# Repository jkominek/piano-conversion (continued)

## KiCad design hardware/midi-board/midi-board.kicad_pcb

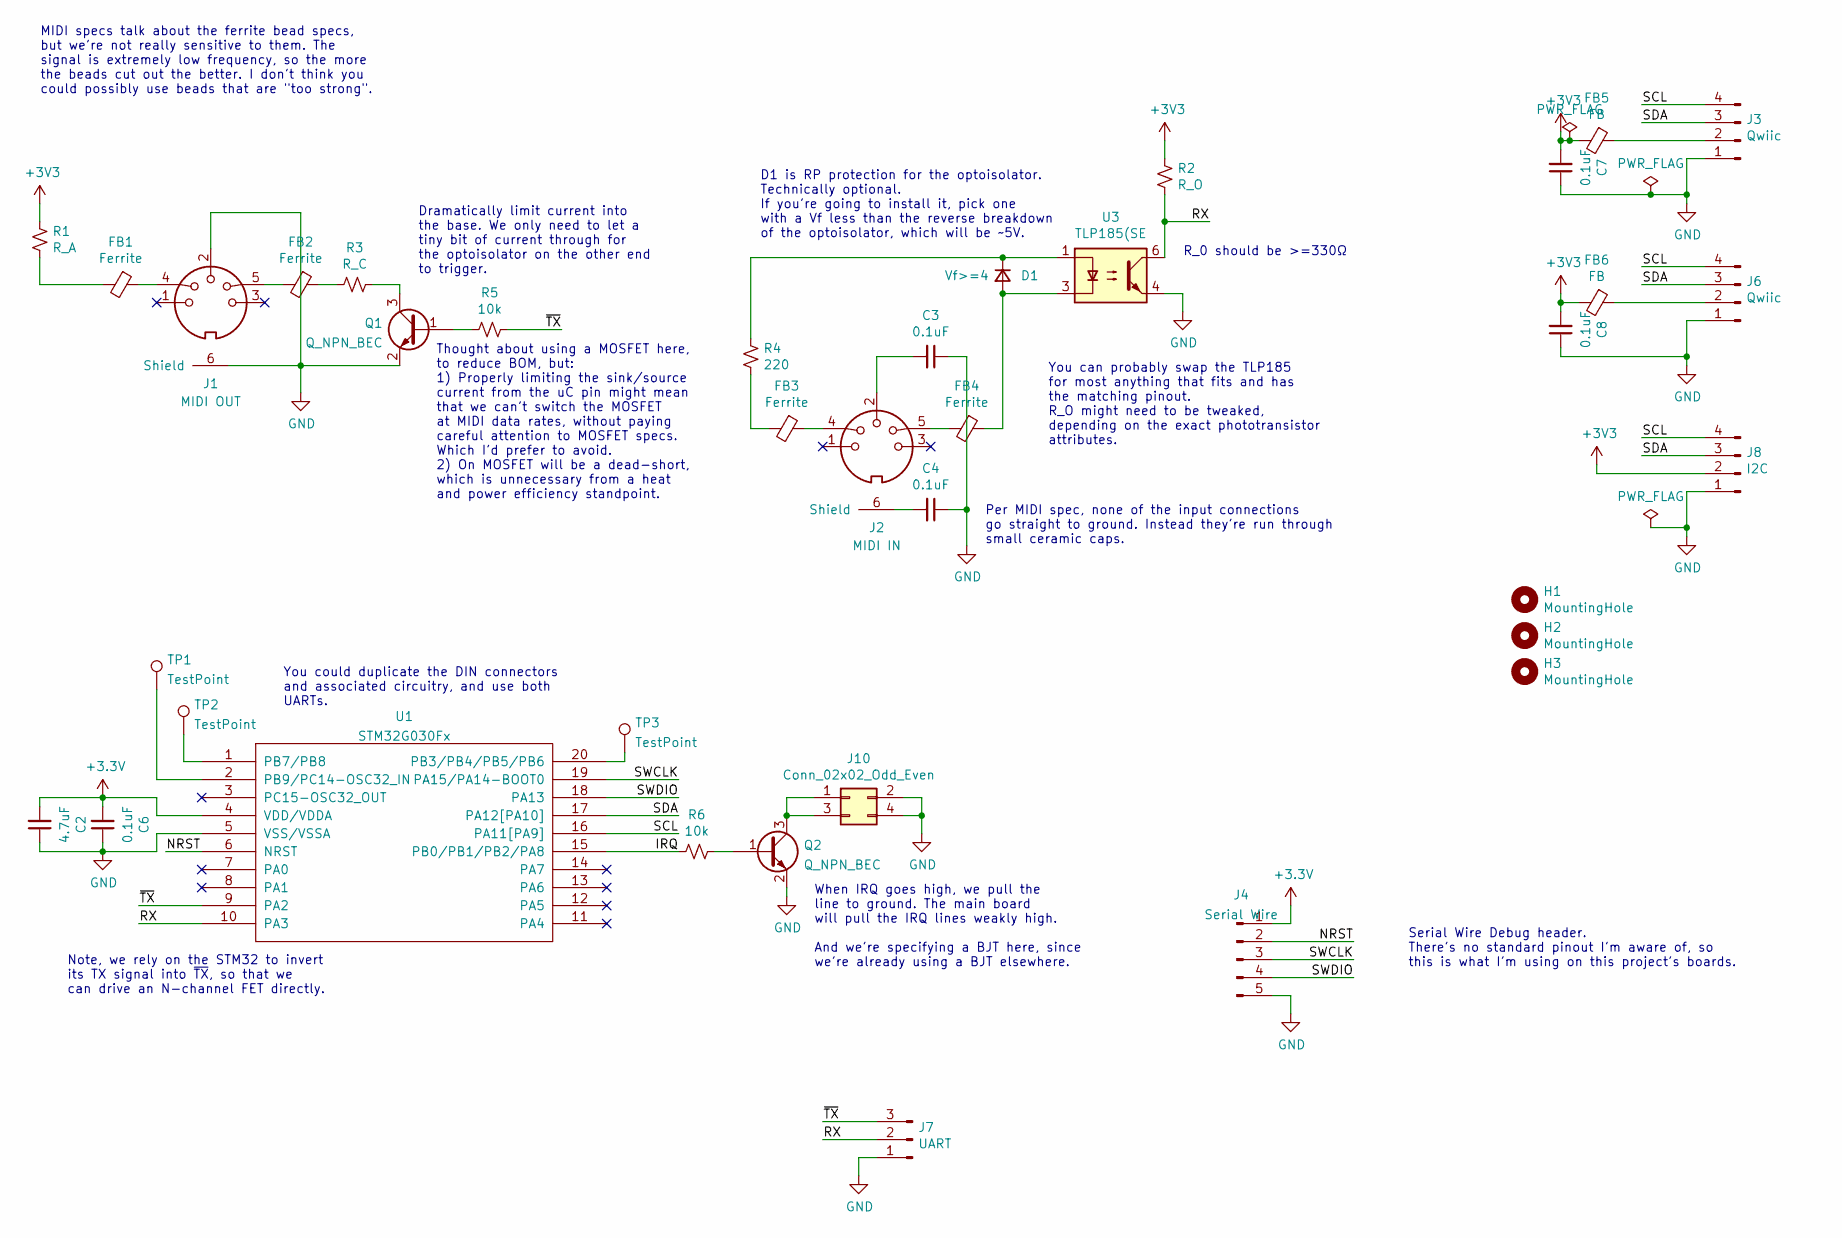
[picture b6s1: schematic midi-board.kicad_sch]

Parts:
C2: 4.7uF; C_0805_2012Metric_Pad1.18x1.45mm_HandSolder
C3, C4, C6, C7, C8: 0.1uF; C_0805_2012Metric_Pad1.18x1.45mm_HandSolder
D1: Vf>=4; D_SOD-123F
FB1, FB2, FB3, FB4: Ferrite; L_0805_2012Metric_Pad1.05x1.20mm_HandSolder
FB5, FB6: FB; L_0805_2012Metric_Pad1.05x1.20mm_HandSolder
H1, H2, H3: MountingHole; MountingHole_3.2mm_M3
J1: MIDI OUT; SDS-50J
J2: MIDI IN; SDS-50J
J3, J6: Qwiic; JST_SH_SM04B-SRSS-TB_04x1.00mm_Angled
J4: Serial Wire; PinHeader_1x05_P2.54mm_Vertical
J7: UART; Pin_Header_Straight_1x03_Pitch2.54mm
J8: I2C; Pin_Header_Straight_1x04_Pitch2.54mm
J10: Conn_02x02_Odd_Even; Pin_Header_Straight_2x02_Pitch2.54mm
Q1, Q2: Q_NPN_BEC; SOT-23
R1: R_A; R_0805_2012Metric_Pad1.20x1.40mm_HandSolder
R2: R_O; R_0805_2012Metric_Pad1.20x1.40mm_HandSolder
R3: R_C; R_0805_2012Metric_Pad1.20x1.40mm_HandSolder
R4: 220; R_0805_2012Metric_Pad1.20x1.40mm_HandSolder
R5, R6: 10k; R_0805_2012Metric_Pad1.20x1.40mm_HandSolder
TP1, TP2, TP3: TestPoint; TestPoint_Pad_D1.0mm
U1: STM32G030Fx; TSSOP-20_4.4x6.5mm_P0.65mm
U3: TLP185(SE; SO-6_4.4x3.6mm_Pitch1.27mm

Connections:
/IRQ: R6.2, U1.15 (PB0/PB1/PB2/PA8)
/NRST: J4.2, U1.6 (NRST)
/RX: J7.2, R2.2, U1.10 (PA3), U3.6
/SCL: J3.4, J6.4, J8.4, U1.16 (PA11[PA9])
/SDA: J3.3, J6.3, J8.3, U1.17 (PA12[PA10])
/SWCLK: J4.3, U1.19 (PA15/PA14-BOOT0)
/SWDIO: J4.4, U1.18 (PA13)
/~TX: J7.3, R5.1, U1.9 (PA2)
GND: C2.1, C3.1, C4.1, C6.1, C7.1, C8.1, J1.2, J1.6 (Shield), J3.1, J4.5, J6.1, J7.1, J8.1, J10.2, J10.4, Q1.2 (E), Q2.2 (E), U1.5 (VSS/VSSA), U3.4
unnamed: C3.2, J2.2
unnamed: C4.2, J2.6 (Shield)
unnamed: D1.1 (K), R4.1, U3.1
unnamed: D1.2 (A), FB4.1, U3.3
unnamed: FB1.1, J1.4
unnamed: FB1.2, R1.2
unnamed: FB2.1, R3.2
unnamed: FB2.2, J1.5
unnamed: FB3.1, J2.4
unnamed: FB3.2, R4.2
unnamed: FB4.2, J2.5
unnamed: FB5.1, J3.2
unnamed: FB6.1, J6.2
unnamed: J10.1, J10.3, Q2.3 (C)
unnamed: Q1.1 (B), R5.2
unnamed: Q1.3 (C), R3.1
unnamed: Q2.1 (B), R6.1
unnamed: TP1.1, U1.2 (PB9/PC14-OSC32_IN)
unnamed: TP2.1, U1.1 (PB7/PB8)
unnamed: TP3.1, U1.20 (PB3/PB4/PB5/PB6)

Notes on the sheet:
MIDI specs talk about the ferrite bead specs, but we're not really sensitive to them. The signal is extremely low frequency, so the more the beads cut out the better. I don't think you could possibly use beads that are "too strong".
When IRQ goes high, we pull the line to ground. The main board will pull the IRQ lines weakly high. And we're specifying a BJT here, since we're already using a BJT elsewhere.
R_0 should be >=330Ω
Per MIDI spec, none of the input connections go straight to ground. Instead they're run through small ceramic caps.
Note, we rely on the STM32 to invert its TX signal into ~{TX}, so that we can drive an N-channel FET directly.
You can probably swap the TLP185 for most anything that fits and has the matching pinout. R_O might need to be tweaked, depending on the exact phototransistor attributes.
Thought about using a MOSFET here, to reduce BOM, but: 1) Properly limiting the sink/source current from the uC pin might mean that we can't switch the MOSFET at MIDI data rates, without paying careful attention to MOSFET specs. Which I'd prefer to avoid. 2) On MOSFET will be a dead-short, which is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
Serial Wire Debug header. There's no standard pinout I'm aware of, so this is what I'm using on this project's boards.
D1 is RP protection for the optoisolator. Technically optional. If you're going to install it, pick one with a Vf less than the reverse breakdown of the optoisolator, which will be ~5V.
Dramatically limit current into the base. We only need to let a tiny bit of current through for the optoisolator on the other end to trigger.
You could duplicate the DIN connectors and associated circuitry, and use both UARTs.

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
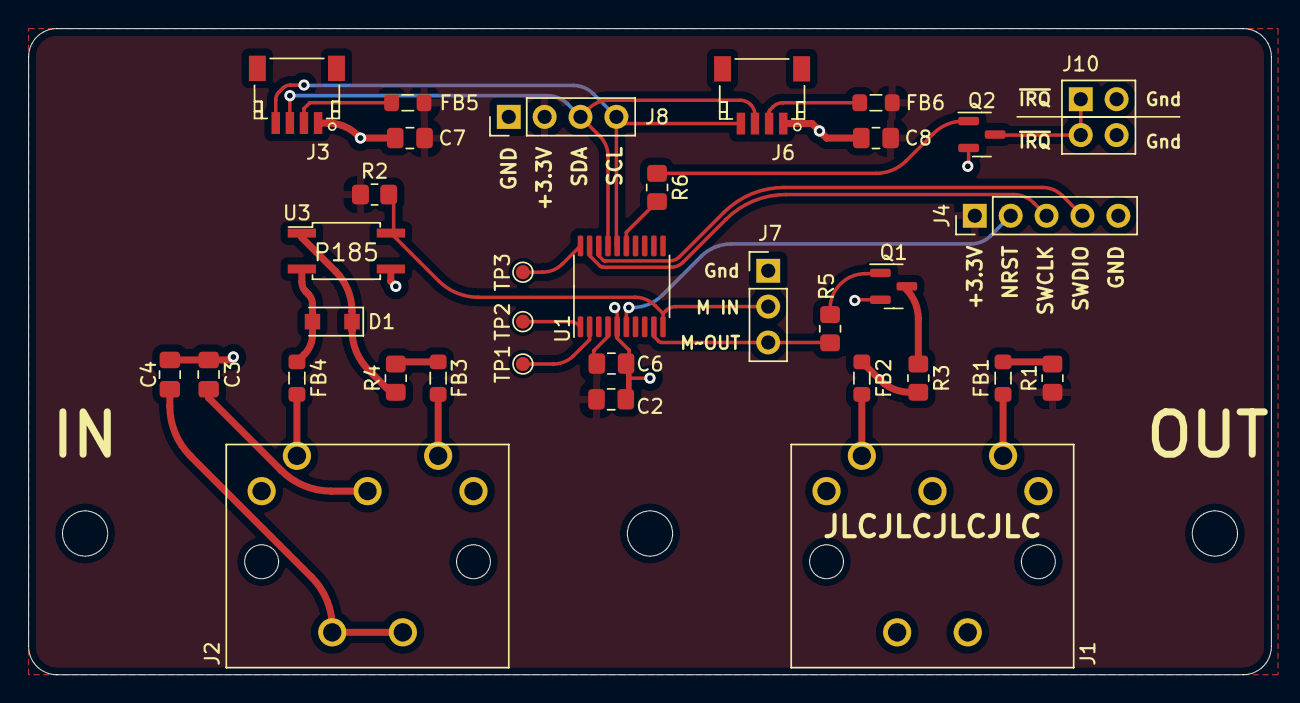
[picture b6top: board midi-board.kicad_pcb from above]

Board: 2 copper layers, 88.0 x 45.8 mm, 37 parts (0 on the bottom side), 30 nets.

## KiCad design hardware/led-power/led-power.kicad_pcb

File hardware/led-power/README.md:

# LED Power board

As covered in the main design doc, the board takes +48V, and uses them
to feed 8 strings of LEDs with a constant current of ~20mA.

# Design

See [the wiki page about the board](https://github.com/jkominek/piano-conversion/wiki/LED-Power-Board) for details on how it works.

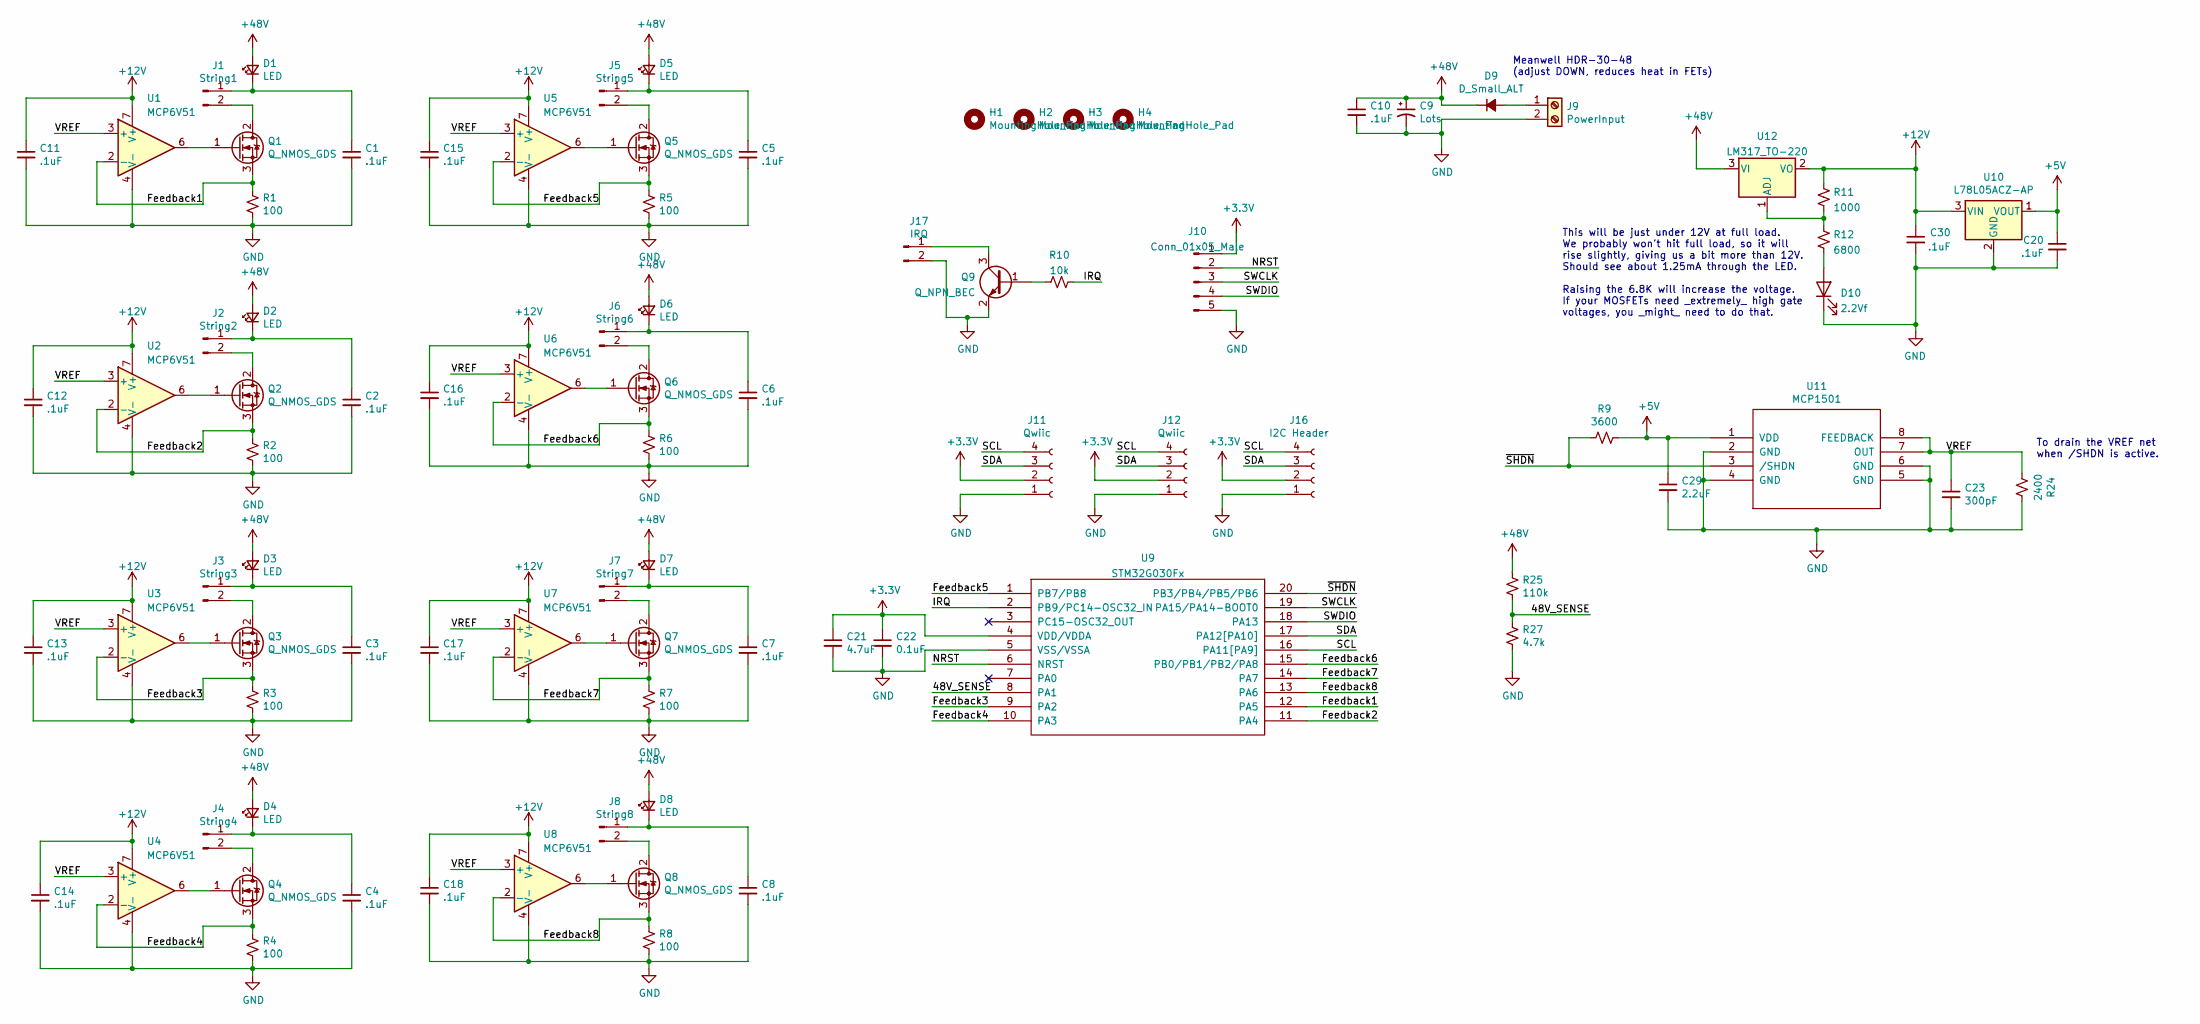
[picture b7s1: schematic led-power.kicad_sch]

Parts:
C1, C2, C3, C4, C5, C6, C7, C8, C10, C11, C12, C13, C14, C15, C16, C17, C18, C20, C30: .1uF; C_0805_2012Metric_Pad1.18x1.45mm_HandSolder
C9: Lots; CP_Radial_D16.0mm_P7.50mm
C21: 4.7uF; C_0805_2012Metric_Pad1.18x1.45mm_HandSolder
C22: 0.1uF; C_0805_2012Metric_Pad1.18x1.45mm_HandSolder
C23: 300pF; C_0805_2012Metric_Pad1.18x1.45mm_HandSolder
C29: 2.2uF; C_0805_2012Metric_Pad1.18x1.45mm_HandSolder
D1, D2, D3, D4, D5, D6, D7, D8: LED; LED_0805_2012Metric_Pad1.15x1.40mm_HandSolder
D9: D_Small_ALT; D_SOD-123F
D10: 2.2Vf; LED_0805_2012Metric_Pad1.15x1.40mm_HandSolder
H1, H2, H3, H4: MountingHole_Pad; MountingHole_3.2mm_M3
J1: String1; Pin_Header_Angled_1x02_Pitch2.54mm
J2: String2; Pin_Header_Angled_1x02_Pitch2.54mm
J3: String3; Pin_Header_Angled_1x02_Pitch2.54mm
J4: String4; Pin_Header_Angled_1x02_Pitch2.54mm
J5: String5; Pin_Header_Angled_1x02_Pitch2.54mm
J6: String6; Pin_Header_Angled_1x02_Pitch2.54mm
J7: String7; Pin_Header_Angled_1x02_Pitch2.54mm
J8: String8; Pin_Header_Angled_1x02_Pitch2.54mm
J9: PowerInput; TerminalBlock_bornier-2_P5.08mm
J10: Conn_01x05_Male; PinHeader_1x05_P2.54mm_Vertical
J11, J12: Qwiic; JST_SH_SM04B-SRSS-TB_04x1.00mm_Angled
J16: I2C Header; Pin_Header_Straight_1x04_Pitch2.54mm
J17: IRQ; Pin_Header_Straight_1x02_Pitch2.54mm
Q1, Q2, Q3, Q4, Q5, Q6, Q7, Q8: Q_NMOS_GDS; TO-220-3_Vertical
Q9: Q_NPN_BEC; SOT-23
R1, R2, R3, R4, R5, R6, R7, R8: 100; R_Axial_DIN0207_L6.3mm_D2.5mm_P2.54mm_Vertical
R9: 3600; R_0805_2012Metric_Pad1.20x1.40mm_HandSolder
R10: 10k; R_0805_2012Metric_Pad1.20x1.40mm_HandSolder
R11: 1000; R_0805_2012Metric_Pad1.20x1.40mm_HandSolder
R12: 6800; R_0805_2012Metric_Pad1.20x1.40mm_HandSolder
R24: 2400; R_0805_2012Metric_Pad1.20x1.40mm_HandSolder
R25: 110k; R_0805_2012Metric_Pad1.20x1.40mm_HandSolder
R27: 4.7k; R_0805_2012Metric_Pad1.20x1.40mm_HandSolder
U1, U2, U3, U4, U5, U6, U7, U8: MCP6V51; MSOP-8_3x3mm_Pitch0.65mm
U9: STM32G030Fx; TSSOP-20_4.4x6.5mm_P0.65mm
U10: L78L05ACZ-AP; TO-92_Inline_Wide
U11: MCP1501; SOIC-8-N
U12: LM317_TO-220; TO-220-3_Vertical

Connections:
+3V3: C21.1, C22.1, J10.1, J11.2, J12.2, J16.2, U9.4 (VDD/VDDA)
+5V: C20.1, C29.1, R9.1, U10.1 (VOUT), U11.1 (VDD)
+12V: C11.1, C12.1, C13.1, C14.1, C15.1, C16.1, C17.1, C18.1, C30.1, R11.1, U1.7 (V+), U2.7 (V+), U3.7 (V+), U4.7 (V+), U5.7 (V+), U6.7 (V+), U7.7 (V+), U8.7 (V+), U10.3 (VIN), U12.2 (VO)
+48V: C9.1, C10.1, D1.2 (A), D2.2 (A), D3.2 (A), D4.2 (A), D5.2 (A), D6.2 (A), D7.2 (A), D8.2 (A), D9.1 (K), R25.1, U12.3 (VI)
/48V_SENSE: R25.2, R27.1, U9.8 (PA1)
/Feedback1: Q1.3 (S), R1.1, U1.2 (-), U9.12 (PA5)
/Feedback2: Q2.3 (S), R2.1, U2.2 (-), U9.11 (PA4)
/Feedback3: Q3.3 (S), R3.1, U3.2 (-), U9.9 (PA2)
/Feedback4: Q4.3 (S), R4.1, U4.2 (-), U9.10 (PA3)
/Feedback5: Q5.3 (S), R5.1, U5.2 (-), U9.1 (PB7/PB8)
/Feedback6: Q6.3 (S), R6.1, U6.2 (-), U9.15 (PB0/PB1/PB2/PA8)
/Feedback7: Q7.3 (S), R7.1, U7.2 (-), U9.14 (PA7)
/Feedback8: Q8.3 (S), R8.1, U8.2 (-), U9.13 (PA6)
/IRQ: R10.2, U9.2 (PB9/PC14-OSC32_IN)
/NRST: J10.2, U9.6 (NRST)
/SCL: J11.4, J12.4, J16.4, U9.16 (PA11[PA9])
/SDA: J11.3, J12.3, J16.3, U9.17 (PA12[PA10])
/SWCLK: J10.3, U9.19 (PA15/PA14-BOOT0)
/SWDIO: J10.4, U9.18 (PA13)
/VREF: C23.1, R24.2, U1.3 (+), U2.3 (+), U3.3 (+), U4.3 (+), U5.3 (+), U6.3 (+), U7.3 (+), U8.3 (+), U11.7 (OUT), U11.8 (FEEDBACK)
/~SHDN: R9.2, U9.20 (PB3/PB4/PB5/PB6), U11.3 (/SHDN)
GND: C1.2, C2.2, C3.2, C4.2, C5.2, C6.2, C7.2, C8.2, C9.2, C10.2, C11.2, C12.2, C13.2, C14.2, C15.2, C16.2, C17.2, C18.2, C20.2, C21.2, C22.2, C23.2, C29.2, C30.2, D10.1 (K), J9.2, J10.5, J11.1, J12.1, J16.1, J17.2, Q9.2 (E), R1.2, R2.2, R3.2, R4.2, R5.2, R6.2, R7.2, R8.2, R24.1, R27.2, U1.4 (V-), U2.4 (V-), U3.4 (V-), U4.4 (V-), U5.4 (V-), U6.4 (V-), U7.4 (V-), U8.4 (V-), U9.5 (VSS/VSSA), U10.2 (GND), U11.2 (GND), U11.4 (GND), U11.5 (GND), U11.6 (GND)
unnamed: C1.1, D1.1 (K), J1.1
unnamed: C2.1, D2.1 (K), J2.1
unnamed: C3.1, D3.1 (K), J3.1
unnamed: C4.1, D4.1 (K), J4.1
unnamed: C5.1, D5.1 (K), J5.1
unnamed: C6.1, D6.1 (K), J6.1
unnamed: C7.1, D7.1 (K), J7.1
unnamed: C8.1, D8.1 (K), J8.1
unnamed: D9.2 (A), J9.1
unnamed: D10.2 (A), R12.2
unnamed: J1.2, Q1.2 (D)
unnamed: J2.2, Q2.2 (D)
unnamed: J3.2, Q3.2 (D)
unnamed: J4.2, Q4.2 (D)
unnamed: J5.2, Q5.2 (D)
unnamed: J6.2, Q6.2 (D)
unnamed: J7.2, Q7.2 (D)
unnamed: J8.2, Q8.2 (D)
unnamed: J17.1, Q9.3 (C)
unnamed: Q1.1 (G), U1.6
unnamed: Q2.1 (G), U2.6
unnamed: Q3.1 (G), U3.6
unnamed: Q4.1 (G), U4.6
unnamed: Q5.1 (G), U5.6
unnamed: Q6.1 (G), U6.6
unnamed: Q7.1 (G), U7.6
unnamed: Q8.1 (G), U8.6
unnamed: Q9.1 (B), R10.1
unnamed: R11.2, R12.1, U12.1 (ADJ)

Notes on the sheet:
Meanwell HDR-30-48 (adjust DOWN, reduces heat in FETs)
This will be just under 12V at full load. We probably won't hit full load, so it will rise slightly, giving us a bit more than 12V. Should see about 1.25mA through the LED. Raising the 6.8K will increase the voltage. If your MOSFETs need _extremely_ high gate voltages, you _might_ need to do that.
To drain the VREF net when /SHDN is active.

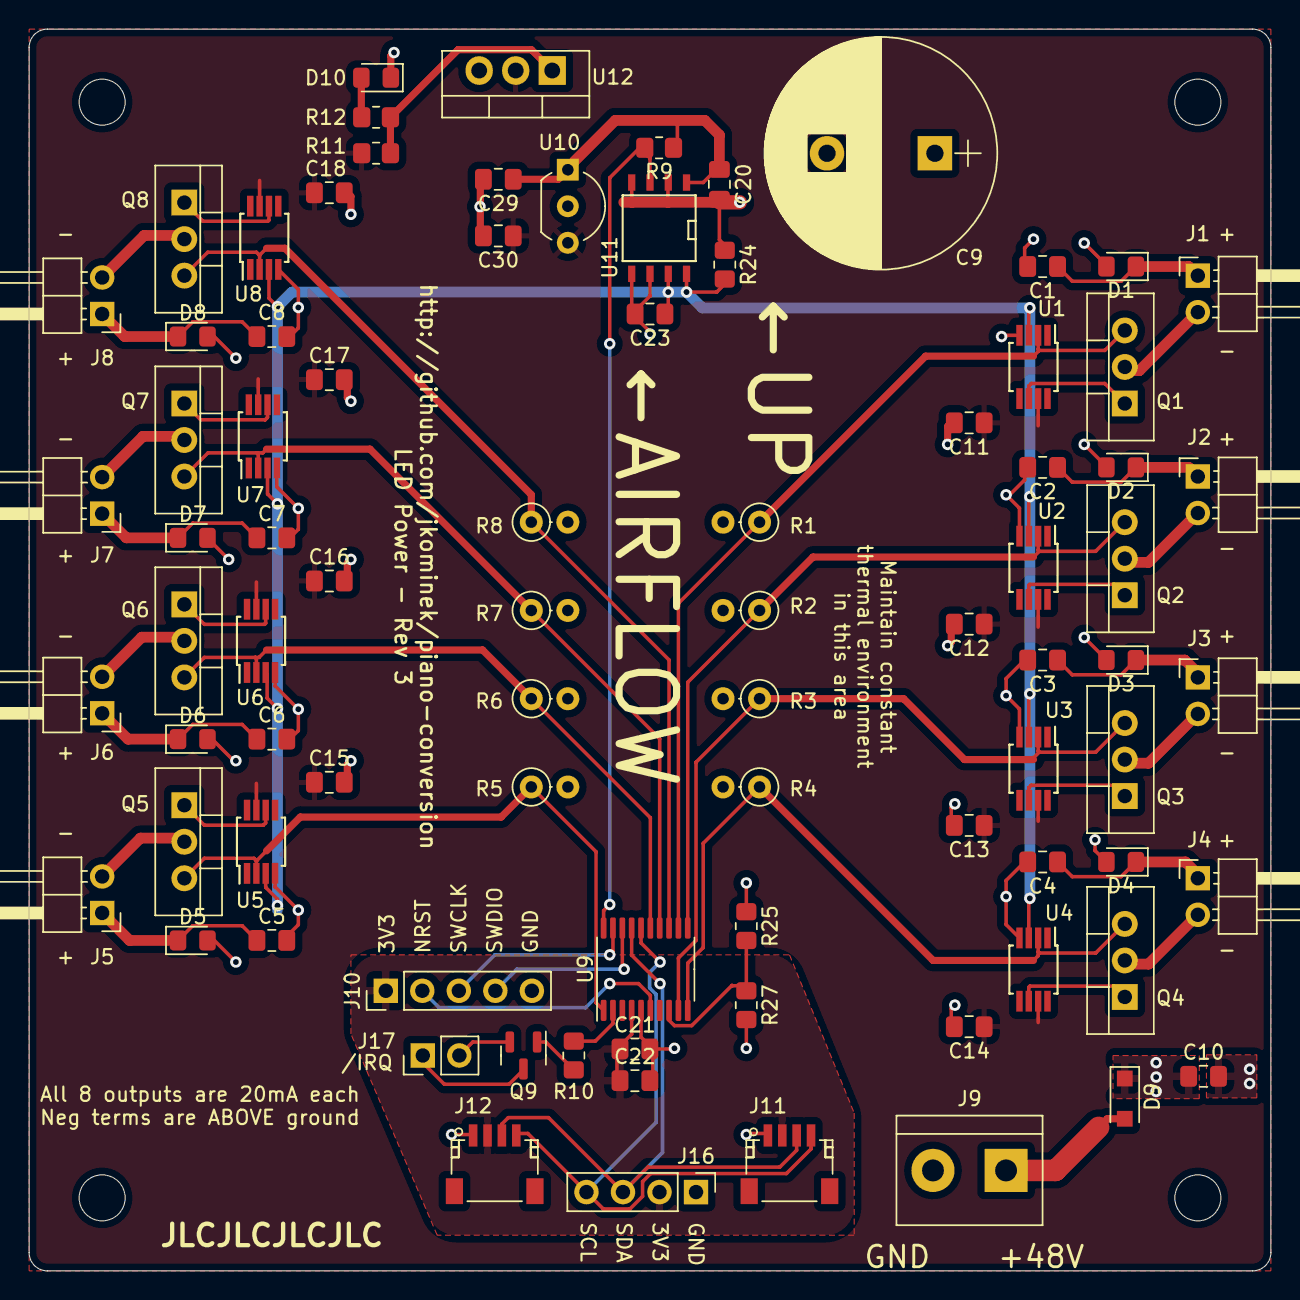
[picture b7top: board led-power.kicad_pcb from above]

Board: 4 copper layers, 86.4 x 86.4 mm, 88 parts (0 on the bottom side), 51 nets.

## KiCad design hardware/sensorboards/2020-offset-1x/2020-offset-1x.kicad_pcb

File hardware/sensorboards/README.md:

# What do we have here?

### For the CNY70 (thru-hole mounting) sensor

* simple-1x
  * A single sensor board that tries to be generically useful
* 2040-centered-1x
  * A single sensor board that centers the sensor across the 40mm wide portion of a 20x40mm tslot aluminum extrusion.
* 2040-centered-2x
  * Same thing, but two sensors on one board.
* 2040-centered-4x
  * Same thing, but four sensors on one board.
* 2040-centered-4x-12deg
  * Same thing, but four sensors on one board and they're rotated 12 degrees, for bass hammers.
* 2020-offset-1x
  * A single sensor board that places the sensor to one side of a 20x20mm extrusion, and the connector on the other side.
* 2020-offset-2x
  * Same thing, but two sensors on one board.
* 2020-offset-4x
  * Same thing, but four sensors on one board.

### For the QRE1113GR (SMT) sensor

* 2040-centered-4x-QRE1113GR
  * Like 2040-centered-4x but with a QRE1113GR instead of CNY70

### For QRE1113 (thru-hole mounting) and EAITRCA6 (thru-hole mounting)

* TBD, note that the pins are the same as in the previous and identical between the two

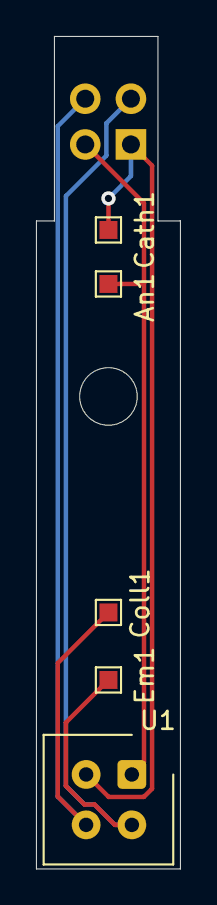
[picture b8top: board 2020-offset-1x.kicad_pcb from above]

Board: 2 copper layers, 8.0 x 46.2 mm, 7 parts (1 on the bottom side), 4 nets.

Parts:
An1: TestPoint; TestPoint_Pad_1.0x1.0mm
Cath1: TestPoint; TestPoint_Pad_1.0x1.0mm
Coll1: TestPoint; TestPoint_Pad_1.0x1.0mm
Em1: TestPoint; TestPoint_Pad_1.0x1.0mm
H1: MountingHole; MountingHole_3.2mm_M3
J1: Conn_02x02_Odd_Even; Pin_Header_Angled_2x02_Pitch2.54mm
U1: CNY70; Vishay_CNY70

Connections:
/Anode: An1.1, J1.3, U1.1
/Cathode: Cath1.1, J1.1, U1.2
/Collector: Coll1.1, J1.4, U1.3
/Emitter: Em1.1, J1.2, U1.4

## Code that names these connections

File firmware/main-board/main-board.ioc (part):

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Mcu.Name=STM32H743ZGTx
Mcu.Package=LQFP144
Mcu.UserName=STM32H743ZGTx
PA11.Mode=Device_Only
PA11.Signal=USB_OTG_FS_DM
PA12.Mode=Device_Only
PA12.Signal=USB_OTG_FS_DP
PA13\ (JTMS/SWDIO).Mode=JTAG_5_pins
PA13\ (JTMS/SWDIO).Signal=DEBUG_JTMS-SWDIO
PA14\ (JTCK/SWCLK).Mode=JTAG_5_pins
PA14\ (JTCK/SWCLK).Signal=DEBUG_JTCK-SWCLK
PA15\ (JTDI).Mode=JTAG_5_pins
PA15\ (JTDI).Signal=DEBUG_JTDI
PA8.Mode=I2C
PA8.Signal=I2C3_SCL
PA9.Mode=Activate_VBUS
PA9.Signal=USB_OTG_FS_VBUS
PB0.GPIOParameters=GPIO_Label
PB0.GPIO_Label=SDCARD_CS
PB0.Signal=GPIO_Output
PB10.GPIOParameters=GPIO_PuPd,GPIO_Label
PB10.GPIO_Label=IIC_EXTI10
PB10.GPIO_PuPd=GPIO_PULLDOWN
PB10.Signal=GPIO_Input
PB11.GPIOParameters=GPIO_PuPd,GPIO_Label
PB11.GPIO_Label=IIC_EXTI11
PB11.GPIO_PuPd=GPIO_PULLDOWN
PB11.Signal=GPIO_Input
PB12.GPIOParameters=GPIO_PuPd,GPIO_Label
PB12.GPIO_Label=IIC_EXTI12
PB12.GPIO_PuPd=GPIO_PULLDOWN
PB12.Signal=GPIO_Input
PB13.GPIOParameters=GPIO_PuPd,GPIO_Label
PB13.GPIO_Label=IIC_EXTI13
PB13.GPIO_PuPd=GPIO_PULLDOWN
PB13.Signal=GPIO_Input
PB14.Mode=Asynchronous
PB14.Signal=USART1_TX
PB15.Mode=Asynchronous
PB15.Signal=USART1_RX
PB3\ (JTDO/TRACESWO).Mode=JTAG_5_pins
PB3\ (JTDO/TRACESWO).Signal=DEBUG_JTDO-SWO
PB4\ (NJTRST).Mode=JTAG_5_pins
PB4\ (NJTRST).Signal=DEBUG_JTRST
PB5.Mode=Asynchronous
PB5.Signal=UART5_RX
PB6.Mode=Asynchronous
PB6.Signal=UART5_TX
PB7.Mode=I2C
PB7.Signal=I2C1_SDA
PB8.Mode=I2C
PB8.Signal=I2C1_SCL
PC0.GPIOParameters=GPIO_Label
PC0.GPIO_Label=LEDSTATUS
PC0.Signal=GPIO_Output
PC10.Mode=Asynchronous
PC10.Signal=UART4_TX
PC11.Mode=Asynchronous
PC11.Signal=UART4_RX
PC12.Mode=SD_1_bit
PC12.Signal=SDMMC1_CK
PC14-OSC32_IN\ (OSC32_IN).Mode=LSE-External-Clock-Source
PC14-OSC32_IN\ (OSC32_IN).Signal=RCC_OSC32_IN
PC6.Mode=Asynchronous
PC6.Signal=USART6_TX
PC7.Mode=Asynchronous
PC7.Signal=USART6_RX
PC8.Mode=SD_1_bit
PC8.Signal=SDMMC1_D0
PC9.Mode=I2C
PC9.Signal=I2C3_SDA
PD14.GPIOParameters=GPIO_Label
PD14.GPIO_Label=PWR3_CTRL
PD14.Signal=GPIO_Output
PD15.GPIOParameters=GPIO_Label
PD15.GPIO_Label=PWR1_CTRL
PD15.Signal=GPIO_Output
PD2.Mode=SD_1_bit
PD2.Signal=SDMMC1_CMD
PD5.Mode=Asynchronous
PD5.Signal=USART2_TX
PD6.Mode=Asynchronous
PD6.Signal=USART2_RX
PD8.Mode=Asynchronous
PD8.Signal=USART3_TX
PD9.Mode=Asynchronous
PD9.Signal=USART3_RX
PE0.Mode=Asynchronous
PE0.Signal=UART8_RX
PE1.Mode=Asynchronous
PE1.Signal=UART8_TX
PE13.GPIOParameters=GPIO_PuPd,GPIO_Label
PE13.GPIO_Label=SDCARD_DET
PE13.GPIO_PuPd=GPIO_PULLDOWN
PE13.Signal=GPIO_Input
PE2.GPIOParameters=GPIO_Label
PE2.GPIO_Label=PWR8_CTRL
PE2.Signal=GPIO_Output
PE3.GPIOParameters=GPIO_Label
PE3.GPIO_Label=PWR6_CTRL
PE3.Signal=GPIO_Output
PE4.GPIOParameters=GPIO_Label
PE4.GPIO_Label=PWR7_CTRL
PE4.Signal=GPIO_Output
PE5.GPIOParameters=GPIO_Label
PE5.GPIO_Label=PWR5_CTRL
PE5.Signal=GPIO_Output
PF0.Mode=I2C
PF0.Signal=I2C2_SDA
PF1.Mode=I2C
PF1.Signal=I2C2_SCL
PF14.Mode=I2C
PF14.Signal=I2C4_SCL
PF15.Mode=I2C
PF15.Signal=I2C4_SDA
PF6.Mode=Asynchronous
PF6.Signal=UART7_RX
PF7.Mode=Asynchronous
PF7.Signal=UART7_TX
PG2.GPIOParameters=GPIO_Label
PG2.GPIO_Label=PWR4_CTRL
PG2.Signal=GPIO_Output
PG3.GPIOParameters=GPIO_Label
PG3.GPIO_Label=PWR2_CTRL
PG3.Signal=GPIO_Output
PH0-OSC_IN\ (PH0).Mode=HSE-External-Clock-Source
PH0-OSC_IN\ (PH0).Signal=RCC_OSC_IN
RCC.HSE_VALUE=20000000
RCC.SYSCLKFreq_VALUE=480000000
RCC.SYSCLKSource=RCC_SYSCLKSOURCE_PLLCLK
board=custom

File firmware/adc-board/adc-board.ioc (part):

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Mcu.Name=STM32H743ZGTx
Mcu.Package=LQFP144
Mcu.UserName=STM32H743ZGTx
PA0.GPIOParameters=GPIO_Label
PA0.GPIO_Label=Sen10
PA0.Mode=IN16-Single-Ended
PA0.Signal=ADC1_INP16
PA1.GPIOParameters=GPIO_Label
PA1.GPIO_Label=Sen11
PA1.Mode=IN17-Single-Ended
PA1.Signal=ADC1_INP17
PA10.GPIOParameters=GPIO_Label
PA10.GPIO_Label=TP27
PA10.Signal=GPIO_Input
PA11.Mode=Device_Only
PA11.Signal=USB_OTG_FS_DM
PA12.Mode=Device_Only
PA12.Signal=USB_OTG_FS_DP
PA13\ (JTMS/SWDIO).Mode=JTAG_5_pins
PA13\ (JTMS/SWDIO).Signal=DEBUG_JTMS-SWDIO
PA14\ (JTCK/SWCLK).Mode=JTAG_5_pins
PA14\ (JTCK/SWCLK).Signal=DEBUG_JTCK-SWCLK
PA15\ (JTDI).Mode=JTAG_5_pins
PA15\ (JTDI).Signal=DEBUG_JTDI
PA2.GPIOParameters=GPIO_Label
PA2.GPIO_Label=Sen12
PA2.Signal=ADCx_INP14
PA3.GPIOParameters=GPIO_Label
PA3.GPIO_Label=Sen9
PA3.Signal=ADCx_INP15
PA4.GPIOParameters=GPIO_Label
PA4.GPIO_Label=Sen8
PA4.Signal=ADCx_INP18
PA5.GPIOParameters=GPIO_Label
PA5.GPIO_Label=Sen7
PA5.Signal=ADCx_INP19
PA6.GPIOParameters=GPIO_Label
PA6.GPIO_Label=Sen6
PA6.Signal=ADCx_INP3
PA7.GPIOParameters=GPIO_Label
PA7.GPIO_Label=Sen5
PA7.Signal=ADCx_INP7
PA8.GPIOParameters=GPIO_Label
PA8.GPIO_Label=TP26
PA8.Signal=GPIO_Input
PA9.Mode=Activate_VBUS
PA9.Signal=USB_OTG_FS_VBUS
PB0.GPIOParameters=GPIO_Label
PB0.GPIO_Label=Sen2
PB0.Signal=ADCx_INP9
PB1.GPIOParameters=GPIO_Label
PB1.GPIO_Label=Sen1
PB1.Signal=ADCx_INP5
PB10.GPIOParameters=GPIO_Label
PB10.GPIO_Label=RS485_TX
PB10.Mode=Asynchronous
PB10.Signal=USART3_TX
PB11.GPIOParameters=GPIO_Label
PB11.GPIO_Label=RS485_RX
PB11.Mode=Asynchronous
PB11.Signal=USART3_RX
PB14.Mode=Asynchronous
PB14.Signal=USART1_TX
PB15.Mode=Asynchronous
PB15.Signal=USART1_RX
PB3\ (JTDO/TRACESWO).Mode=JTAG_5_pins
PB3\ (JTDO/TRACESWO).Signal=DEBUG_JTDO-SWO
PB4\ (NJTRST).Mode=JTAG_5_pins
PB4\ (NJTRST).Signal=DEBUG_JTRST
PC0.GPIOParameters=GPIO_Label
PC0.GPIO_Label=Sen14
PC0.Signal=ADCx_INP10
PC1.GPIOParameters=GPIO_Label
PC1.GPIO_Label=Sen13
PC1.Signal=ADCx_INP11
PC10.GPIOParameters=PinState,GPIO_Label
PC10.GPIO_Label=LED4
PC10.PinState=GPIO_PIN_SET
PC10.Signal=GPIO_Output
PC12.GPIOParameters=GPIO_Label
PC12.GPIO_Label=LED3
PC12.Signal=GPIO_Output
PC4.GPIOParameters=GPIO_Label
PC4.GPIO_Label=Sen4
PC4.Signal=ADCx_INP4
PC5.GPIOParameters=GPIO_Label
PC5.GPIO_Label=Sen3
PC5.Signal=ADCx_INP8
PC8.GPIOParameters=GPIO_Label
PC8.GPIO_Label=TP28
PC8.Signal=GPIO_Input
PC9.GPIOParameters=GPIO_Label
PC9.GPIO_Label=TP25
PC9.Signal=GPIO_Input
PD5.Mode=Asynchronous
PD5.Signal=USART2_TX
PD6.Mode=Asynchronous
PD6.Signal=USART2_RX
PE0.GPIOParameters=GPIO_Label
PE0.GPIO_Label=LED2
PE0.Signal=GPIO_Output
PE1.GPIOParameters=GPIO_Label
PE1.GPIO_Label=LED1
PE1.Signal=GPIO_Output
PF10.GPIOParameters=GPIO_Label
PF10.GPIO_Label=Sen15
PF10.Mode=IN6-Single-Ended
PF10.Signal=ADC3_INP6
PF3.GPIOParameters=GPIO_Label
PF3.GPIO_Label=Sen22
PF3.Mode=IN5-Single-Ended
PF3.Signal=ADC3_INP5
PF4.GPIOParameters=GPIO_Label
PF4.GPIO_Label=Sen21
PF4.Mode=IN9-Single-Ended
PF4.Signal=ADC3_INP9
PF5.GPIOParameters=GPIO_Label
PF5.GPIO_Label=Sen20
PF5.Mode=IN4-Single-Ended
PF5.Signal=ADC3_INP4
PF6.GPIOParameters=GPIO_Label
PF6.GPIO_Label=Sen19
PF6.Mode=IN8-Single-Ended
PF6.Signal=ADC3_INP8
PF7.GPIOParameters=GPIO_Label
PF7.GPIO_Label=Sen18
PF7.Mode=IN3-Single-Ended
PF7.Signal=ADC3_INP3
PF8.GPIOParameters=GPIO_Label
PF8.GPIO_Label=Sen17
PF8.Mode=IN7-Single-Ended
PF8.Signal=ADC3_INP7
PF9.GPIOParameters=GPIO_Label
PF9.GPIO_Label=Sen16
PF9.Mode=IN2-Single-Ended
PF9.Signal=ADC3_INP2
PG7.GPIOParameters=GPIO_Label
PG7.GPIO_Label=TP23
PG7.Signal=GPIO_Input
PG8.GPIOParameters=GPIO_Label
PG8.GPIO_Label=TP24
PG8.Signal=GPIO_Input
RCC.HSE_VALUE=8000000
RCC.SYSCLKFreq_VALUE=480000000
RCC.SYSCLKSource=RCC_SYSCLKSOURCE_PLLCLK
board=custom

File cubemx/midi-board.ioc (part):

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Mcu.Name=STM32G030F6Px
Mcu.Package=TSSOP20
Mcu.UserName=STM32G030F6Px
PA0.Signal=GPIO_Output
PA1.Signal=GPIO_Output
PA11\ [PA9].Mode=I2C
PA11\ [PA9].Signal=I2C2_SCL
PA12\ [PA10].Mode=I2C
PA12\ [PA10].Signal=I2C2_SDA
PA13.Mode=Serial_Wire
PA13.Signal=SYS_SWDIO
PA14-BOOT0.Mode=Serial_Wire
PA14-BOOT0.Signal=SYS_SWCLK
PA2.Mode=Asynchronous
PA2.Signal=USART2_TX
PA3.Mode=Asynchronous
PA3.Signal=USART2_RX
PA4.Mode=IN4
PA4.Signal=ADC1_IN4
PA5.Mode=IN5
PA5.Signal=ADC1_IN5
PA6.Mode=IN6
PA6.Signal=ADC1_IN6
PA7.Mode=IN7
PA7.Signal=ADC1_IN7
PB0.Signal=GPIO_Output
PB6.Mode=Asynchronous
PB6.Signal=USART1_TX
PB7.Mode=Asynchronous
PB7.Signal=USART1_RX
PC14-OSC32_IN\ (PC14).Signal=GPIO_Output
PC15-OSC32_OUT\ (PC15).Signal=GPIO_Output
RCC.HSE_VALUE=8000000
RCC.SYSCLKFreq_VALUE=16000000
board=custom

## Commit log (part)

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2020-11-01 rearranging some of the text
2020-11-01 a single-sensor board
2020-11-02 tweak some peripheral settings
2020-11-03 rearrange the schematic for viewability
2020-11-09 adc board schematic tweaks and complete relayout
2020-11-09 protective mosfet on power input. all THT parts
2020-11-14 correct RS485 termination resistors, adjust ground pours
2020-11-17 first rev of reasonable new LED power board
2020-11-17 alternative power inputs; cap on NRST; 3.3V reg thermal work on PCB
2020-11-17 update design notes a bit
2020-11-17 move USB ferrite closer to connector; add VCC pad near BOOT pulldown
2020-11-19 Rev0 of boards; added text
2020-12-03 switch to STM32H743, add GPIO and missing periph, label GPIO and analog pins
2020-12-03 fix missing ground in rev0; adjust silk screen for readability
2020-12-04 Lots of LED power bring-up corrections
    * MSOP-8 footprint for op amps
    * TO-220 footprint for FETs
    * Moved C10 away from J9
    * Stopped bothering with length-adjusted traces to resistors
    * Moved diodes away from LED strip terminals
    * Silkscreen tweaks
2020-12-06 Add a header for measuring current to ADC board
2020-12-06 Significant copper pour tweaks, and packing traces in tighter
2020-12-09 Add MIDI board
2020-12-09 project-wide library of symbols and footprints
2020-12-09 adding some multimedia
2020-12-10 IRQ & Clock adjustments
2020-12-13 new footprints
    * double-stacked 8p8c connector for mainboard
    * 1/4" TRS jack for pedal board
2020-12-13 Correct 5V regulator orientation and give the GND pin more thermal relief.
    Slightly rearranged the traces coming out of the MCP1501.
2020-12-13 Convert pedal board over to I2C/Qwiic. Adjust mounting hole spacing.
2020-12-13 Complete pedal board I2C conversion; make I2C address configurable.
2020-12-13 Converted MIDI board to I2C
2020-12-14 alternate uart symbol for the midi board. not sure why i did this
2020-12-15 shrunk the sensorboard slightly, removed extra mounting hole.
2020-12-16 Swap power filter caps, tighten up trace routing
2020-12-16 convert to surface mount caps for power filtration
2020-12-18 Fix swapped RS485 Z/Y pins. Add reset supervisor and 4 pin USB header.
2020-12-18 Swap USART1 and USART3 on RS485 connection, so that main board has bootloader access.
2020-12-18 Rearrange pin labels to reflect new usage.
2020-12-18 Copper pours, and some clippable pads for the lowest voltage.
2020-12-18 Second Qwiic header, semi-split analog power rail, silkscreen tweaks.
2020-12-20 Silkscreen improvements for usability
2020-12-20 Narrowed the board, better matching Cybrid's dimensions.
2020-12-20 Made I2C address configurable to match other boards, tweaked silkscreen
2020-12-21 Fix UART and I2C pin errors. Add ETH INTRP and RXER pins.
    Various vias added, and passives packed in better around the ethernet.
2020-12-21 Had the p-channel FETs in the wrong orientation, and an unnecessary resistor.
2020-12-21 Removed some unused nets and marked the pins NC
2020-12-21 Tweak some copper pour boundaries and trace routing.
2020-12-23 Updated design doc
2021-01-15 CubeMX project for the main board
2021-01-16 MicroSD card slot and some IRQ headers.
2021-01-17 Rev 2 changes
    * Pulldown on VREF so that ~SHDN can work
    * Voltage dividers on the rails, fed to the MCP23017 so it can detect faults
    * Increased space between Qwiic headers
    * Bring I2C bus out on 0.100" header
    * Tweaked LED positions on the left side; right seemed to be fine.
    * Converted it to a four layer board. +15V/GND/GND/+48V
2021-01-19 MIDI board Rev 1 changes
    * Standardize mounting hole spacing
    * Change 74LVC1G06 to 74LVC1G07 in schematic
    * Expose ~IRQ headers
    * Increase Qwiic header space
    * Improve TLP185(SE footprint; remove unused pads, label orientation
    * Bring I2C out on a header.
2021-01-20 Rev 1 first batch of changes
    - Made it narrower, but had to expand the space between mounting holes.
    - Moved the jacks back 2.3mm.
    - 10mm to board edge, 5mm clearance on the inside of the board, 7.5mm clearance on either side
    - Fixed the outline to be silkscreen, not a hole in the mask
    - Added I2C bus header
    - Made nice little three pad footprints for spots where you need a pull up or a pull down.
2021-01-21 Tweak some traces, and bump the board rev
2021-01-21 Cleanup and reconcile the headers. Switch to SOT23 regulators for both.
2021-01-21 Tweak a bunch of traces, bump the board rev
2021-02-28 drop OptoDevice parts besides the CNY70
2021-02-28 update the README a bit
2021-12-27 generate plot
2021-12-27 simple 3-channel adc capture in a loop
2021-12-27 more useful interval, and time to collect its value
2021-12-27 data without any object near the sensors
2021-12-27 CLI filenames
2021-12-27 use subdirectory
2021-12-27 legend - tested also by sending the corresponding ADC input to ground
2021-12-27 oscillating with a larger, metal object
2021-12-27 label placement and correlation x axis
2021-12-28 not cut off the legend on some OSes
2021-12-29 stub to real-time plotting
2021-12-29 interactive display
2021-12-29 two lines
2021-12-29 arbitrary number of sensors
2021-12-29 works with multiple panels, but it is too slow
2021-12-29 serial communication stub
2021-12-29 parsing data from the RPi
2021-12-29 actual serial connection settings
2021-12-29 the serial port returns bytes, not string objects
2021-12-30 stub for playing notes
2021-12-31 housekeeping wrt file management
2021-12-31 clearer messages
2022-01-01 correct saving of the header message to file when using hw
2022-01-01 preparing for plotting 9 sensors (available now as dummy data)
2022-01-01 removed unnecessary prints of the prefix
2022-01-01 plots from the first tries
2022-01-01 data and plots from the tries in the back action
2022-01-01 old capture without source
2022-01-01 Preliminary measurements
2022-01-02 clarified why smaller is better
2022-01-02 explaining why no plot for open space
2022-01-02 Fixing some words and conclusions
2022-01-21 ADC Board to Kicad 6; made corrections for updated DRC & ERC.
2022-01-21 First bit of public data, and a small analysis/dev script
2022-01-24 Including some OpenSCAD files for 3D printed parts I've used.
2022-01-28 adcreceive can now handle any number of boards
2022-01-30 Built about half of automatic calibration.
    Fixed a bug in HDLC processing.
    Started splitting the python script out into different programs.
2022-02-02 Update 4x boards for issue #44; introduce the 12deg rotated hammer board
2022-02-04 Made issue #44 changes to sensorboards, introduced 3x versions
    Also finished bringing them up to Kicad 6.0
2022-02-04 Move from TIM4 to TIM1, allowing ADCs to run out of phase.
    Also instead of processing HDLC data continuously, we turn on
    the character match interrupt for USART3, and have the handler
    process HDLC data, saving CPU cycles.
2022-02-04 Include some files which had been omitted previously.
2022-02-11 First draft of the automatic sensor board creator script.
2022-02-13 Unified ground nets in schematic and layout.
    * Rearranged the layers that pours are on.
    * Added the keep-out zone separating analog and
    digital areas from each other.
    * Tightened up placement of decoupling capacitors.
2022-02-14 LED power board improvements, per issue #42
    * Increased thermal relief
    * Moved C10 well away from J9
    * R24 and R9 are now the same value, 3.6kohm
    * Removed R0
    * Removed the need for the +15V supply with an LM317.
    * Removed I2C IO expander and replaced with an STM32G0
2022-02-16 Made most changes for rev 2 of MIDI board
    * Silkscreen for I2C header
    * Converted from specialized I2C UART to an STM32G0
    * Replace the specialized 74-series open-drain buffer with a BJT
    * Switch to using a BJT to pull down the interrupt line.
2022-02-16 Made changes for pedal board rev 2, per issue #40
    * 1uF caps on all the incoming signal lines
    * Switched to STM32G0 from the I2C ADC
    * Added IRQ support, with transistor for pull down
    * Every TRS pin is brought to an ADC pin, so we can attempt autodetection
    of pedal behavior.
2022-02-16 Update READMEs and such.
    Also include a forgotten symbol library file.
2022-02-16 More ADC board rev 3 changes, per issue #47
    * 4.5V regulator for phototransistors
    * new 3.3V regulator for analog section
    * new 2.0V precision voltage reference
    * Analog voltages and their distribution rearranged
    * Tidied up traces on the left hand side, everything is nice and curvy now
    * Adjusted USB ESD protection to be optional and/or support other parts
2022-02-20 main board changes for rev 2 per issue #41
    * Added a bit more thermal relief to everything on the top layer
    * Looked at the RS485 and I2C caps thermal relief and called it good enough.
    * Fixed silkscreen of C20 and most everything else, as I upgraded to KiCad 6 footprints and the refs all moved.
    * Changed the ferrite bead footprint to the handsoldering one.
    * Tweaked the specified values for the Pwr and Stat LEDs, but not much.
    * Removed battery connector and associated bits.
2022-02-22 ADC board layout tweaks; rearranged the various power planes
    * Moved to standard plane layout of power, ground, ground, power,
    which I should've done from the start.
    * Removed pads from the mounting holes, don't want to risk ground
    loops through the frame, there's no value.
    * Adjusted the position of the 3.3VA regulator.
    * Tweaked/tightened up a lot of traces, trying to keep them shorter.
2022-02-24 Removing CubeMX file for main board that used the wrong processor.
2022-02-25 Convenience tool for analyzing net lists for correctness
2022-04-24 Next revs of the important boards
    Includes some tiny DRC tweaks for the LED power board.
2022-06-04 rearrange files
2022-06-04 convert calibrator.py over to using util.py
2022-06-05 Fix bug in HDLC DMA transmit for issue #51
2022-06-26 goofy attempt to use QRE1113GR sensors
2022-07-03 QRE1113GR 2x sensorboards, with four holes for added stability
2022-07-04 - using straight, rather than angled, connector - adjusted the board size - included 3D models - added a README and a raytracing model of the board
2022-07-05 implementing comments from https://pianoclack.com/forum/d/542-update-on-piano-conversion/12
2022-07-05 suggestions from https://pianoclack.com/forum/d/542-update-on-piano-conversion/ for the 2x board too
2022-07-16 removed stale, old files, still using the CNY70
2022-07-16 layer selection and drill (I think)
2022-07-16 larger board for back action
2022-07-17 increasing resolution, using parameters -- more to come
2022-07-17 no, sadly can do the rendering only in KiCad, because there is no way to do in in OpenSCAD or FreeCAD because of format incompatibilities, grrrrr :((( With OpenSCAD or FreeCAD at most we can get an i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
2022-07-18 converting OpenSCAD-generated QRE1113-screen.stl file to KiCad-liked QRE1113-screen.wrl using FreeCAD as scripted in convert_stl_to_wrl.py, oh my!
2022-07-18 positioned screen and extrusions
2022-07-18 renamed to avoid confusion with the actual board
2022-07-18 ignoring the correct files
2022-07-18 comments and reorg of variables
2022-07-18 whitespace to make more readable
2022-07-18 modularized the bolt holes and bolt head groove
2022-07-18 parametrize z position of bolt head groove on half screen thickness
2022-07-18 ignoring pycache created by freecad
2022-07-18 parametrized X distance in between holes (which by the way is identical, triple-checked in KiCad
2022-07-18 modified position, pretty close but not perfect and still problem of scale
2022-07-18 align guide lines, labels next to the connector and thicker footprint, all on the silkscreen
2022-07-18 programmatically setting the scale per KiCad bug https://github.com/KiCad/kicad-packages3D/issues/405
2022-07-18 still a 1% was unaccounted, sigh
2022-07-18 making the width of the screen nominally the same of the KiCad PCB
2022-07-18 named sensor hole in preparation of splitting it in two
2022-07-18 further parametrization and adjustment of values, still with inconsistencies
2022-07-23 final slight alignment to get the screen exactly in front of the board
2022-07-23 clarified exact Y position of the bolt holes
2022-07-23 adjusted size of the sensorholes and their y position on the screen
2022-07-23 sloppy grooves for the pins (on wrong side of the board and misaligned) just to get started
2022-07-23 added another screen to show bottom, enlarged mock 3D model of QRE1113 which is not accurate
2022-07-23 better parametrized depth of the groove for the QRE1113 pins
2022-07-23 slightly enlarging the clearance for the sensor, and significantly for its pins
2022-07-23 Adopting Jay's names and directory locations
2022-07-23 protector is a clearer word than screen
2022-07-24 ignoring remaining silkscreen overlaps
2022-07-24 silkscreen on the back of the board
2022-07-24 gerber preferences by PCBway
